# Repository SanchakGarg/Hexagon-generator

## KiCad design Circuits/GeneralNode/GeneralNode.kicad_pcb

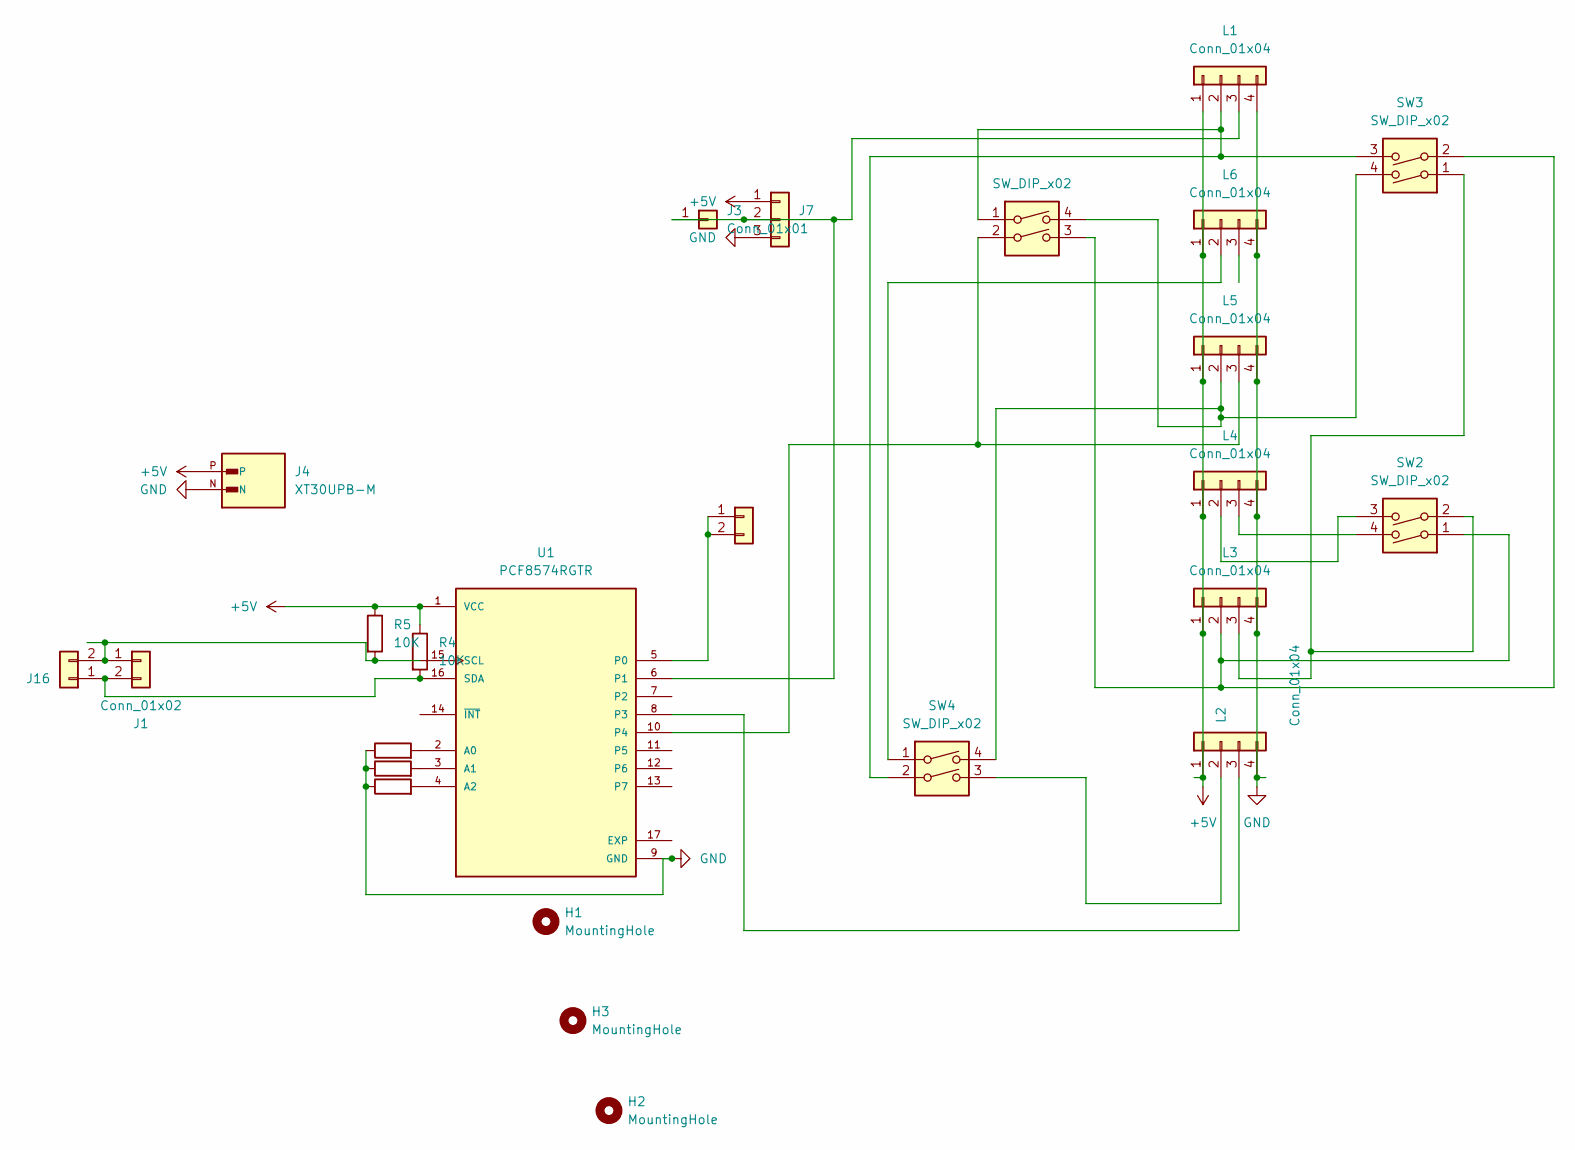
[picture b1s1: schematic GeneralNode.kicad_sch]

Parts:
H1, H2, H3: MountingHole; MountingHole_3.2mm_M3
J1, J16: Conn_01x02; PinSocket_1x02_P2.54mm_Vertical
J2: Conn_01x02; PinHeader_1x02_P2.54mm_Vertical
J3: Conn_01x01; PinHeader_1x01_P2.54mm_Vertical
J4: XT30UPB-M; AMASS_XT30UPB-M
J7: Conn_01x03; PinSocket_1x03_P2.54mm_Vertical
L1, L2, L3, L4, L5, L6: Conn_01x04; Molex_KK-254_AE-6410-04A_1x04_P2.54mm_Vertical
R1, R2, R3: 10K; R_0805_2012Metric
R4, R5: 10K; R_0603_1608Metric
SW1, SW2, SW3, SW4: SW_DIP_x02; SW_DIP_SPSTx02_Slide_6.7x6.64mm_W7.62mm_P2.54mm_LowProfile
U1: PCF8574RGTR; QFN50P300X300X100-17N; PARTREV J

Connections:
+5V: J4.P, J7.1, L1.1, L2.1, L3.1, L4.1, L5.1, L6.1, R4.1, R5.1, U1.1 (VCC)
GND: J4.N, J7.3, L1.4, L2.4, L3.4, L4.4, L5.4, L6.4, R1.1, R2.1, R3.1, U1.9 (GND)
unnamed: J1.1, J16.2, R5.2, U1.15 (SCL)
unnamed: J1.2, J16.1, R4.2, U1.16 (SDA)
unnamed: J2.1, J2.2, U1.5 (P0)
unnamed: J3.1 (Pin_1_1), J7.2, L1.3, U1.6 (P1)
unnamed: L1.2, SW1.1, SW3.3, SW4.2
unnamed: L2.2, SW4.3
unnamed: L2.3, U1.8 (P3)
unnamed: L3.2, SW1.3, SW2.1, SW3.2
unnamed: L3.3, SW2.2, SW3.1
unnamed: L4.2, SW2.3
unnamed: L4.3, SW2.4
unnamed: L5.2, SW1.4, SW3.4, SW4.4
unnamed: L5.3, SW1.2, U1.10 (P4)
unnamed: L6.2, SW4.1
unnamed: R1.2, U1.2 (A0)
unnamed: R2.2, U1.3 (A1)
unnamed: R3.2, U1.4 (A2)

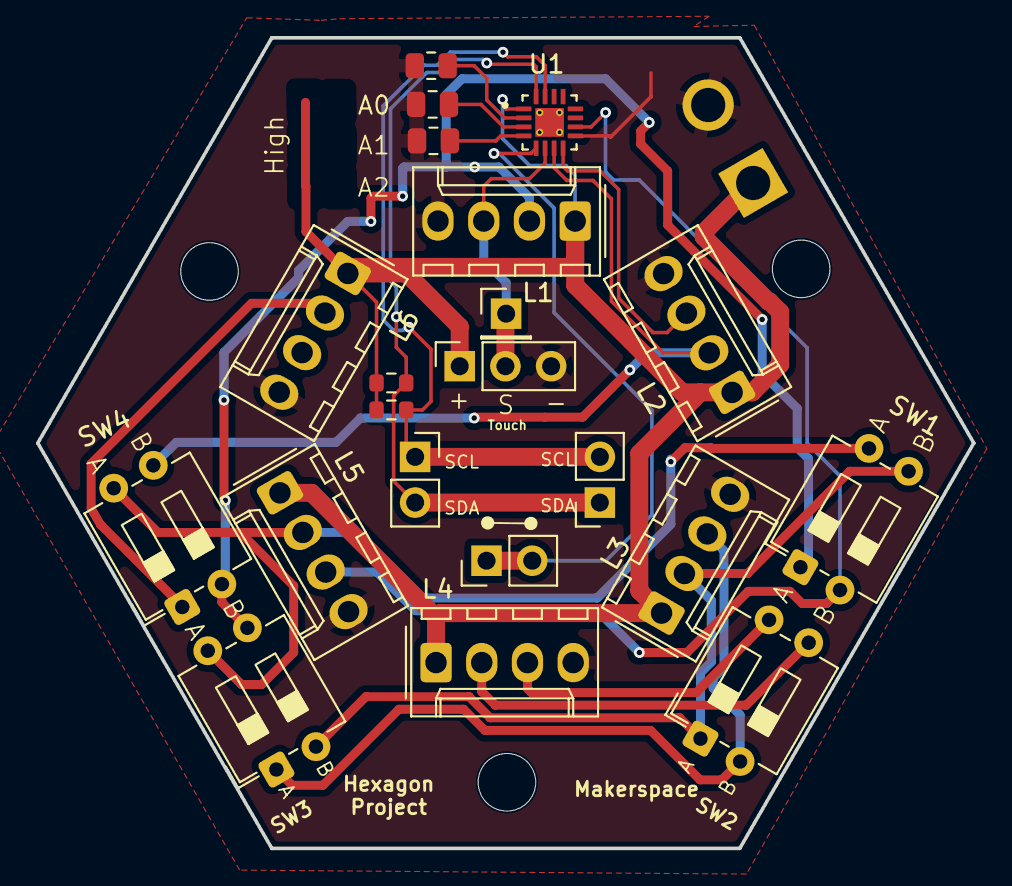
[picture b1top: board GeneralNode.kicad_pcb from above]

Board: 2 copper layers, 52.0 x 45.0 mm, 25 parts (1 on the bottom side), 19 nets.

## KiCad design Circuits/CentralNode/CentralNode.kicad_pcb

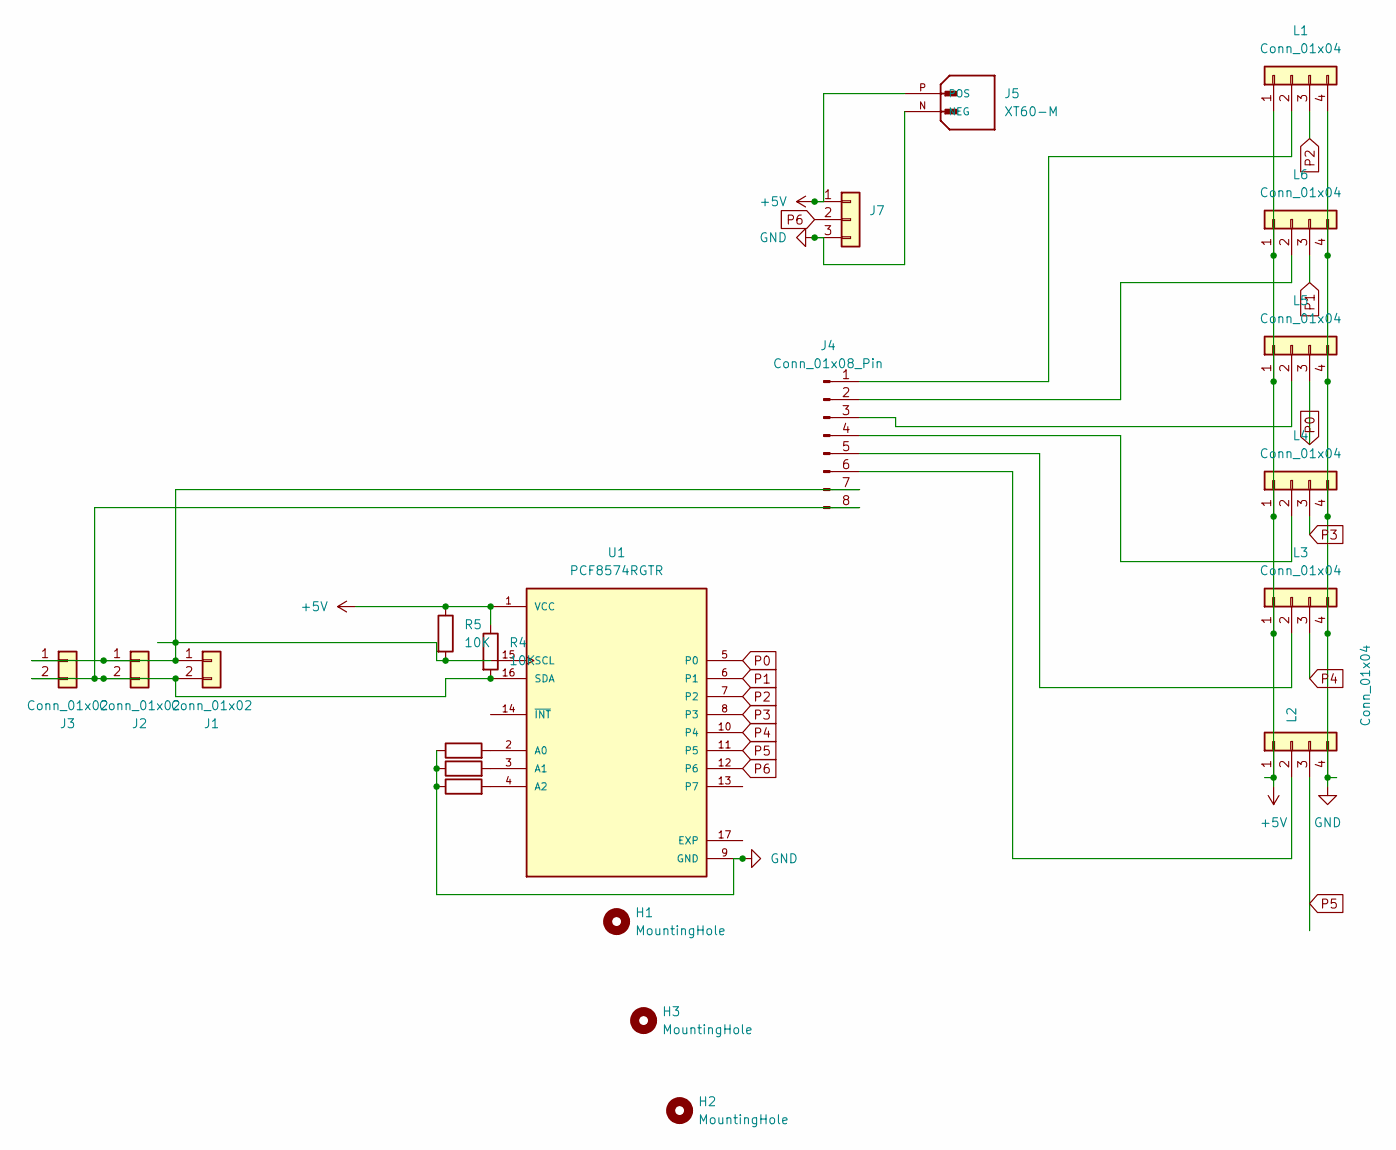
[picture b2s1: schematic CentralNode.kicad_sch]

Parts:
H1, H2, H3: MountingHole; MountingHole_3.2mm_M3
J1, J2, J3: Conn_01x02; PinSocket_1x02_P2.54mm_Vertical
J4: Conn_01x08_Pin; JST_EH_B8B-EH-A_1x08_P2.50mm_Vertical
J5: XT60-M; AMASS_XT60-M; PARTREV V1.2
J7: Conn_01x03; PinSocket_1x03_P2.54mm_Vertical
L1, L2, L3, L4, L5, L6: Conn_01x04; Molex_KK-254_AE-6410-04A_1x04_P2.54mm_Vertical
R1, R2, R3: 10K; R_0805_2012Metric
R4, R5: 10K; R_0603_1608Metric
U1: PCF8574RGTR; QFN50P300X300X100-17N; PARTREV J

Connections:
+5V: J5.P (POS), J7.1, L1.1, L2.1, L3.1, L4.1, L5.1, L6.1, R4.1, R5.1, U1.1 (VCC)
GND: J5.N (NEG), J7.3, L1.4, L2.4, L3.4, L4.4, L5.4, L6.4, R1.1, R2.1, R3.1, U1.9 (GND)
unnamed: J1.1, J2.1, J3.1, J4.7, R5.2, U1.15 (SCL)
unnamed: J1.2, J2.2, J3.2, J4.8, R4.2, U1.16 (SDA)
unnamed: J4.1, L1.2
unnamed: J4.2, L6.2
unnamed: J4.3, L5.2
unnamed: J4.4, L4.2
unnamed: J4.5, L3.2
unnamed: J4.6, L2.2
unnamed: R1.2, U1.2 (A0)
unnamed: R2.2, U1.3 (A1)
unnamed: R3.2, U1.4 (A2)
P0: L5.3, U1.5 (P0)
P1: L6.3, U1.6 (P1)
P2: L1.3, U1.7 (P2)
P3: L4.3, U1.8 (P3)
P4: L3.3, U1.10 (P4)
P5: L2.3, U1.11 (P5)
P6: J7.2, U1.12 (P6)

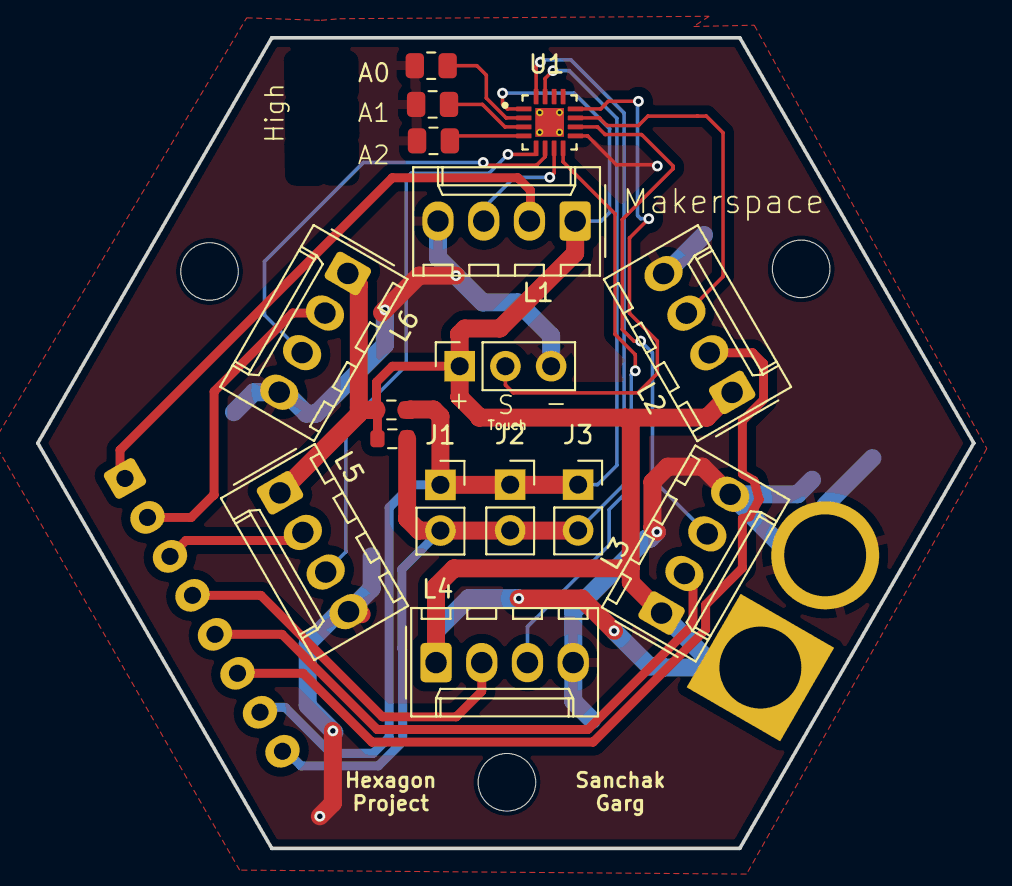
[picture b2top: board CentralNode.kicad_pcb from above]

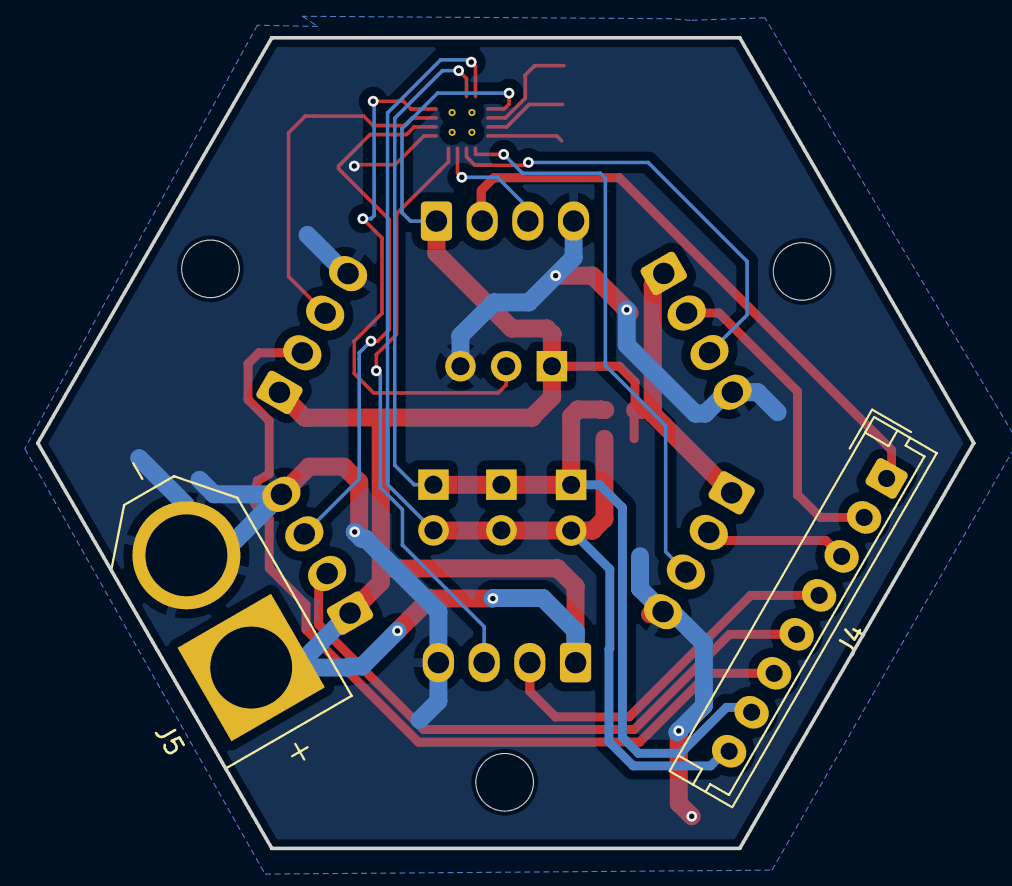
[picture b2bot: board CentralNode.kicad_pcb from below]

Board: 2 copper layers, 52.0 x 45.0 mm, 21 parts (2 on the bottom side), 20 nets.
